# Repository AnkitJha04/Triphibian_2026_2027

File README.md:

# BE Capstone Project

## Project Title

RiftWalker: The Triphibious Bot

---

## Team Details

| Sr. No. | Name of Student | Roll No. | Branch                   | Email ID                      |
|---------|-----------------|----------|--------------------------|-------------------------------|
| 1       | Ankit Jha       | 41       | Automation and Robotics  | 2023.ankitkumar.jha@ves.ac.in |
| 1       | Nidhi Kulkarni  | 15       | Automation and Robotics  | 2023.nidhi.kulkarni@ves.ac.in |
| 1       | Yadnyee Joshi   | 10       | Automation and Robotics  | 2023.yadnyee.joshi@ves.ac.in  |
| 1       | Dnyanam Gala    | 36       | Automation and Robotics  | 2023.dnyanam.gala@ves.ac.in   |

---

## Guide Details

**Project Guide: Mrs. Sangeeta Prasanna Ram**  
**Department:** Automation and Robotics  
**Institute:** VESIT, Mumbai  

---

## Problem Statement

The objective of this project is to create an innovative, small unmanned robotic system that can function in air, land, and water domains through a unified propulsion and control mechanism and thus eliminates the requirement of using different systems such as UAV, UGV, and surface water vehicles in multi-environment missions.

Traditional unmanned systems are usually designed to work in one environment only. While the UAV offers high-speed flying abilities, it lacks endurance; the land robot offers efficiency but is limited by terrain; and the surface vehicle is incapable of crossing land barriers.

Recent studies have shown that integration of these two technologies is possible; however, triphibious robots are far fewer in number compared to dual-environment robots since integration leads to more weight and complexity in design and control, in addition to increased energy consumption.

---

## Abstract

Unmanned robotic systems are being increasingly employed for surveillance purposes, inspection tasks, emergency rescue operations and monitoring of the environment. But since most of these platforms are designed for one environment only, which could be air, land or water, missions in complex environments would either necessitate the use of multiple vehicles or halt the mission as the platform encounters the environment it cannot negotiate. It has been shown through studies on multimodal robots that multimodality is useful in increasing accessibility but it brings with it some difficulties in terms of weight, efficiency, mechanics and control.

The Riftwalker is a prototype of a triphibious robotic platform that aims to study movement in air, land and surface water using the same vehicle architecture. The platform uses four brushless motors as the source of propulsion in aerial environment while servo motors are used to orient the motors for different modes of operation. Passive wheels help the robot move on the ground while elements providing buoyancy help the robot operate in surface water environment.

The current design target has an approximately 2.2 kg maximum take-off mass, with calculated/design-stage performance targets of approximately 58 km/h aerial speed, 78 km/h peak ground speed and 10 km/h surface-water speed. These values will be treated as design targets until experimentally validated.

The expected outcome is a functional prototype demonstrating controlled movement and transition between three operating domains for applications including search and rescue, environmental surveying, inspection and remote reconnaissance.

Youtube video link :- https://youtu.be/WmMp18_r6lU

---

## Objectives

1. To study existing **multimodal and triphibious robotic platforms** and identify the challenges associated with integrating aerial, terrestrial and surface-water mobility into a single robotic system.

2. To develop a **3D CAD model** of the RiftWalker incorporating the structural frame, BLDC motor assemblies, servo-based tilting mechanism, wheels, buoyancy elements and electronics enclosure.

3. To design a **servo-based thrust vectoring mechanism** that changes the orientation of the BLDC propulsion units to enable different modes of locomotion using a unified propulsion system.

4. To perform **engineering calculations and feasibility analysis** including component-wise weight estimation, thrust-to-weight ratio, servo torque, battery and power requirements, land mobility, and water buoyancy.

5. To develop a custom **ESP32-S3 based flight controller PCB** integrating power management, motor and servo interfaces, USB-C programming, battery voltage monitoring and required sensor interfaces.

6. To integrate onboard sensors including the **MPU6050 IMU, magnetometer, barometer, ultrasonic sensor and water sensor** for orientation, altitude, obstacle and environmental-state monitoring.

7. To validate the proposed mechanical and electronic design through **simulation, PCB ERC/DRC verification and prototype testing**, ensuring that the system meets the defined design requirements.

8. To fabricate and integrate the mechanical, electronic and control subsystems and evaluate the **air, land and surface-water operating modes** of the RiftWalker prototype.

9. To document the complete design process, calculations, implementation, testing and results, and identify **future improvements and applications** of the proposed multi-terrain robotic platform.

---

## Scope of the Project

This project will cover the following key areas:

1) **3D mechanical design** and development of the servo-based thrust vectoring mechanism.
2) Selection and integration of **BLDC motors, ESCs, servos, wheels and buoyancy elements**.
3) Design of a custom **ESP32-S3 based flight controller PCB** with sensor, motor and servo interfaces.
4) Integration of sensors including **MPU6050, magnetometer, barometer, ultrasonic and water sensors**.
5) **Engineering calculations and simulation** for weight, thrust, torque, power and buoyancy.
6) Prototype fabrication, hardware integration and **testing of air, land and water operation**.
7) Performance evaluation and documentation of the developed system.

---

## Existing System

Existing unmanned robotic systems are generally designed for operation in a specific environment. They can broadly be classified as follows:

| Platform          | Strength                                               | Main Limitation                                             |
|------------------ |------------------------------------------------------- |------------------------------------------------------------ |
| UAV               | Fast aerial movement and access to difficult locations | High energy consumption and limited endurance               |
| UGV               | Efficient and stable terrestrial operation             | Restricted by water, steep terrain and other obstacles      |
| USV               | Efficient operation on surface water                   | Limited terrestrial mobility                                |
| Dual-Mode Robot   | Capable of operating in two environments               | Cannot independently access the third environment           |
| Triphibious Robot | Potential to operate in air, land and water            | Higher mass, mechanical complexity and control requirements |

Research has demonstrated the feasibility of combining multiple modes of locomotion within a single robotic platform. Existing triphibious and multimodal systems have explored approaches such as shared propulsion systems, tilting or morphing mechanisms and integrated mobility structures.

However, combining three different modes of locomotion introduces several engineering challenges, particularly in terms of **weight, energy efficiency, mechanical complexity, controllability and endurance**.

# Limitations of Existing Systems

1. **Multiple System Requirement:** Using separate UAV, UGV and waterborne platforms increases equipment, transportation and operational complexity.

2. **Limited Endurance:** Aerial systems require continuous thrust to remain airborne, resulting in significant power consumption.

3. **Terrain Limitations:** Ground robots may be restricted by water or difficult terrain, while waterborne platforms cannot easily overcome land-based obstacles.

4. **Increased Mechanical Complexity:** Combining separate propulsion and mobility mechanisms for different environments can increase the overall weight, power requirements and mechanical complexity of the system.

These limitations motivate the development of **RiftWalker**, which investigates the feasibility of combining aerial, terrestrial and surface-water mobility within a single robotic platform while sharing major propulsion, power and control components.

---

## Proposed System

RiftWalker proposes one reconfigurable vehicle rather than three independent vehicles.

Main Idea
The same central platform carries the battery, controller, communication system, sensors and propulsion hardware through all operating modes. Components are reused wherever practical rather than adding an independent propulsion system for every environment.

Operating Principle :
Air Mode
Four A2212-class 1400 KV BLDC motors with 9050 propellers operate in a multicopter configuration. The present design calculations indicate approximately 4.72 kg combined maximum static thrust against a 2.20 kg MTOW, corresponding to a calculated thrust-to-weight ratio of approximately 2.15:1.

Land Mode
The vehicle lands onto its wheel system. Servo-controlled propulsion orientation redirects available thrust to generate terrestrial motion rather than requiring a completely separate high-power traction architecture.

Water Mode
Buoyant wheel/body elements keep the electronics and major structure above the waterline while redirected propulsion produces forward motion across the water surface.

Control System : 
An ESP32-S3-class controller is currently proposed for prototype-level control, handling functions such as:
1) Stabilization/PID control,
2) IMU and navigation sensor processing,
3) Propulsion commands,
4) Servo actuation,
5) Mode management,
6) Telemetry,
7) Waypoint navigation.

Expected Benefits :

The expected benefit is mobility flexibility rather than superior performance in every individual domain.

A purpose-built UAV will likely fly more efficiently, a dedicated UGV can achieve better terrestrial endurance, and a purpose-built USV will generally perform better on water. RiftWalker instead investigates whether somewhat reduced domain-specific efficiency can be accepted in exchange for one platform being able to continue a mission when the terrain changes.
That is a much stronger and more realistic technical proposition.

---

## System Architecture

                    ┌─────────────────────┐
                    │   HUMAN OPERATOR    │
                    │ Ground Control / UI │
                    └──────────┬──────────┘
                               │
                     Telemetry / Commands
                               │
                               ▼
                  ┌────────────────────────┐
                  │ ONBOARD CONTROL SYSTEM │
                  │      ESP32-S3          │
                  │                        │
                  │ • Mission Logic        │
                  │ • PID / Stabilization  │
                  │ • Sensor Fusion        │
                  │ • Mode Management      │
                  │ • Navigation           │
                  └───────┬────────┬───────┘
                          │        │
                 ┌────────┘        └───────────┐
                 ▼                             ▼
        ┌─────────────────┐          ┌─────────────────┐
        │ SENSOR SYSTEM   │          │ ACTUATION       │
        │                 │          │ SYSTEM          │
        │ IMU             │          │                 │
        │ GNSS / NavIC    │          │ 4 × ESC         │
        │ Altitude        │          │ 4 × BLDC        │
        │ Camera*         │          │ Vector Servos   │
        └─────────────────┘          └────────┬────────┘
                                             │
                         ┌───────────────────┼──────────────────┐
                         ▼                   ▼                  ▼
                    AIR MODE            LAND MODE          WATER MODE
                    Multirotor          Wheels +           Buoyancy +
                    Flight              Vector Thrust      Vector Thrust
                         │                   │                  │
                         └───────────────────┼──────────────────┘
                                             ▼
                                  MULTI-DOMAIN MOBILITY

                     ┌─────────────────────────────┐
                     │       POWER SYSTEM          │
                     │  4S 6200 mAh LiPo Battery   │
                     │  Power Distribution / BEC   │
                     └─────────────────────────────┘

## System Architecture

The RiftWalker system architecture is divided into four main sections:

Control System: The onboard controller acts as the brain of the robot. It processes sensor data, manages stabilization and navigation, controls propulsion, and switches between air, land, and water modes.
Sensor & Navigation System: Sensors such as the IMU and GNSS/NavIC provide information about orientation, position, motion, and vehicle state. Additional cameras or perception sensors can be integrated for autonomous navigation.
Propulsion & Actuation System: Four BLDC motors with ESCs generate thrust. Servo mechanisms change the direction of the propulsion system depending on the operating mode—vertical thrust for flight and redirected thrust for movement on land or water.
Power & Communication System: A 4S 6200 mAh LiPo battery supplies the motors, servos, controller, and sensors. A wireless telemetry link allows the ground operator to send commands and receive vehicle data.

Overall, the architecture is designed around sharing the same propulsion, power, sensing, and control hardware across all three environments, reducing the need for separate systems for each mode.

---

## Hardware Requirements

| Sr. No. | Component               | Specification                      | Quantity | Purpose                                           |
| ------- | ----------------------- | ---------------------------------- | -------- | ------------------------------------------------- |
| 1       | BLDC Motor              | A2212, 1400 KV                     |        4 | Common propulsion for air, land and water         |
| 2       | Propeller               | 9050, matched to motor             |        4 | Generates aerodynamic thrust                      |
| 3       | ESC                     | 4S-compatible, appropriately rated |        4 | Controls BLDC motor speed                         |
| 4       | LiPo Battery            | 4S, 6200 mAh                       |        1 | Main onboard power source                         |
| 5       | Microcontroller         | ESP32-S3                           |        1 | Main control, sensor processing and telemetry     |
| 6       | IMU                     | 6/9-axis accelerometer + gyroscope |        1 | Orientation, motion and stabilization             |
| 7       | Sensor (Water/Distance) | Relevent to the use case           |        1 | Outdoor positioning and navigation                |
| 8       | Servo Motors            | High-torque, metal-gear            |        4 | Changes propulsion orientation between modes      |
| 9       | Wheels                  | Lightweight passive/free-rolling   |        4 | Supports terrestrial locomotion                   |
| 10      | Buoyancy System         | Lightweight waterproof floats/body |    1 set | Provides stability and flotation on water         |
| 11      | Power Distribution/BEC  | 4S compatible                      |        1 | Distributes and regulates electrical power        |
| 12      | Telemetry System        | Wireless bidirectional link        |        1 | Operator commands and vehicle telemetry           |
| 13      | Camera                  | Lightweight onboard camera         |        1 | Visual feedback/perception                        |
| 14      | Frame & Mounting System | Lightweight rigid structure        |        1 | Supports all mechanical and electronic components |
| 15      | Flight Controller       | Custom                             |        1 | For functioning of everything perfectly           |
---

## Software Requirements

| Sr. No. | Software / Tool          | Version           | Purpose                                          |
| ------- | ------------------------ | ----------------- | ------------------------------------------------ |
| 1       | Arduino IDE / PlatformIO | Current stable    | ESP32-S3 firmware development                    |
| 2       | Embedded C/C++           | Current toolchain | Low-level control and sensor interfacing         |
| 3       | Python                   | 3.x               | Data analysis, testing and algorithm prototyping |
| 4       | MATLAB / Simulink        | Available release | Modelling, PID tuning and system analysis        |
| 5       | Inventor                 | Available release | Mechanical CAD and assembly design               |
| 6       | KiCad                    | Current stable    | PCB and electronic system design                 |
| 7       | Git / GitHub             | Current stable    | Version control and project documentation        |
| 8       | SimScale / OpenFOAM      | Current stable    | Computational Fluid Dynamics (CFD) simulation    |
| 9       | Wokwi                    | Current stable    | Headless hardware testing prior to flashing.     |

---

## Technologies Used

1. **Embedded Systems:** ESP32-S3 and Embedded C/C++ for vehicle control and sensor interfacing.
2. **Sensor Integration & Control:** Integration of IMU, magnetometer, barometer, ultrasonic and water sensors for vehicle-state monitoring and control.
3. **PID Control:** PID-based stabilization and control of the propulsion system and vehicle motion.
4. **PCB Design (EDA):** KiCad for schematic design, component selection, PCB layout, routing and ERC/DRC verification.
5. **CAD & Mechanical Design:** Autodesk Inventor for 3D modelling, assembly design and development of the mechanical structure.
6. **Thrust Vectoring:** Servo-controlled motor orientation for redirecting propulsion across different operating modes.
7. **Multirotor Propulsion:** BLDC motors, ESCs and propellers for aerial propulsion.
8. **Power Management:** Separate logic and servo power domains with battery voltage monitoring and regulated power supplies.
9. **Wireless Communication:** Wireless communication for vehicle control and telemetry.
10. **Simulation & Engineering Analysis:** Mechanical and system-level analysis along with calculations for weight, thrust-to-weight ratio, servo torque, power requirements and buoyancy.

---

## Methodology

1. **Literature Survey:** Study existing multimodal and triphibious robotic platforms to understand their propulsion mechanisms, mobility approaches, control strategies and limitations.
2. **Problem Identification and Requirement Analysis:** Identify the major challenges involved in combining air, land and water mobility and establish the mechanical, electrical and performance requirements of RiftWalker.
3. **Concept Development:** Evaluate different multi-terrain mechanisms and finalize the use of a unified BLDC propulsion system with a **servo-based thrust vectoring mechanism**.
4. **Mechanical Design:** Develop the **3D CAD model in Fusion 360**, including the structural frame, motor mounts, servo tilting mechanism, wheels, buoyancy elements and electronics enclosure.
5. **Engineering Analysis:** Perform weight estimation, thrust-to-weight ratio, servo torque, battery and power, land mobility and buoyancy calculations to evaluate the feasibility of the proposed design.
6. **Simulation and Design Validation:** Validate the proposed mechanical concept and operating principle through simulation and analysis, and modify the design based on the obtained results.
7. **Electronic System Development:** Design the custom **ESP32-S3 based flight controller PCB** in KiCad, including power management, motor and servo interfaces, sensor interfaces, USB-C programming and battery monitoring.
8. **PCB Verification and Hardware Integration:** Perform schematic checks, ERC/DRC verification and PCB routing, followed by fabrication and integration of the controller with the motors, servos, sensors and power system.
9. **Firmware and Control Development:** Develop the ESP32-S3 firmware for sensor processing, stabilization, motor and servo control, communication and operating-mode management.
10. **Testing and Validation:** Test the integrated prototype in air, land and surface-water modes and evaluate parameters such as stability, mobility, thrust-vectoring response, power consumption and transition behaviour.
11. **Performance Analysis and Documentation:** Compare experimental results with calculated design values, identify limitations and improvements, and document the complete design, implementation and testing process.

---

## Project Timeline

| Week / Month |                      Task Planned                                  | Status      |
|--------------|--------------------------------------------------------------------|-------------|
| **Week 1**   | Problem Finalization & Project Planning                            | Completed   |
| **Week 2**   | Literature Survey & Research Paper Review                          | Completed   |
| **Week 3**   | Requirement Analysis & Component Selection                         | Completed   |
| **Week 4**   | Engineering Calculations                                           | Completed   |
| **Week 5**   | Mechanical Design & 3D CAD Modelling                               | Completed   |
| **Week 6**   | Simulation & Design Validation                                     | Completed   |
| **Week 7**   | Flight Controller PCB Design & Schematic Development               | Completed   |
| **Week 8**   | PCB Routing, ERC/DRC Verification & Hardware Procurement           | Completed   |
| **Week 9**   | PCB ic finalization & Component Weight testing                     | Completed   |
| **Week 10**  | PCB Fabrication & Assembly                                         | In Progress |
| **Week 11**  | Hardware Integration & Sensor Interfacing                          | In Progress |
| **Week 12**  | Firmware Development & System Testing                              | In Progress |
| **Week 13**  | Final Testing, Documentation & Project Demonstration               | Pending     |
| **Week 14**  | Research Paper Writing & Project Documentation                     | Pending     |
| **Week 15**  | Final Presentation & Project Demonstration                         | Pending     |

---

## Weekly Progress Updates

Students must update this section every week.
| Week  | Date        |                  Work Completed                |             Next Week         |         Issues / Challenges       | GitHub Commit |
|------ |------------ |----------------------------------------------- |------------------------------ |---------------------------------- |-------------- |
| **1** | 22/06–28/06 | Problem finalization & planning                | Literature survey             | Concept feasibility               | —             |
| **2** | 29/06–05/07 | Literature survey & paper review               | Requirement analysis          | Mobility vs. weight               | —             |
| **3** | 06/07–12/07 | Requirements & components finalized            | Engineering calculations      | Weight, thrust & cost             | —             |
| **4** | 13/07–19/07 | Weight, thrust, torque & buoyancy calculations | Mechanical design             | Maintaining low weight            | —             |
| **5** | 20/07–26/07 | 3D CAD model & mechanical design               | Design validation & PCB       | Mechanism integration             | —             |
| **6** | 27/07–02/08 | Design validation & simulation                 | PCB schematic                 | Mechanical-electronic integration | —             |
| **7** | 03/08–09/08 | ESP32-S3 schematic & component selection       | PCB routing & verification    | GPIO & power management           | —             |
| **8** | 10/08–16/08 | PCB routing, ERC/DRC & documentation           | PCB fabrication & procurement | Routing & component placement     | —             |
| **9** | 17/08–23/08 | Finalized and Completed PCB design verification| Working on software           | Component availability            | —             |
| **10**| 24/08–30/08 | Made control center to control/code the drone  | PCB fabrication & procurement | Software needs and api development| —             |

---

## Design Files

| File Type             | File Name / Link                                 | Description                                          |
|--                     |---                                               |---                                                   |
| **CAD Model**         | [Autodesk Inventor CAD Files](hardware/CAD/)     | 3D mechanical model and assembly of RiftWalker       |
| **Circuit Diagram**   | [Circuit Diagram ](images/circuit_diagram-2.jpg) | Custom ESP32-S3 flight-controller schematic          |
| **PCB Design**        | [KiCad PCB Files](hardware/PCB/)                 | Custom flight-controller PCB design and routing      |
| **ERC / DRC Reports** | [PCB Verification Files](hardware/PCB/)          | Electrical and design rule verification reports      |
| **Flowchart**         | [System Flowchart](images/flowchart.jpeg)        | Proposed operating sequence and control flow         |
| **Simulation File**   | [Wokwi Simulation Files](software/simulation/)   | ESP32-based simulation files for preliminary testing |        

---

## Circuit Diagram

---

## Flowchart / Algorithm

### Algorithm

1. System Initialization – Power up the ESP32-S3 and initialize the IMU, GNSS/NavIC, altitude sensor, ESCs, servos and communication modules.
2. Self-Test & Health Check – Verify sensor communication, battery voltage, telemetry link and actuator status. Prevent arming if a critical fault is detected.
3. Standby / Arm – Keep propulsion disabled until a valid arm command and mission/operator command are received.
4. Sensor Acquisition – Continuously collect orientation, acceleration, altitude, position and other available sensor measurements.
5. Sensor Fusion & State Estimation – Combine measurements to estimate the robot's attitude, position, velocity and motion state.
6. Control Loop – Run the feedback controllers at high frequency to calculate the required thrust, attitude and motion corrections.
7. Mode Decision – Determine whether Air, Land or Water mode is requested/appropriate. For the prototype, operator-confirmed switching is safer than claiming fully autonomous terrain classification.
8. Execute Selected Mode – In Air Mode, operate as a multirotor; in Land Mode, redirect thrust and use the wheels; in Water Mode, maintain flotation and use vectored thrust for surface movement.
9. Navigation – Follow manual commands or mission waypoints while continuously updating the required heading, speed and position.
10. Safety Monitoring – Continuously check battery level, communication link, attitude, actuator/current limits and other available health information.
11. Failsafe Handling – If a critical fault occurs, execute the safest response available for the current mode, such as controlled landing, stopping propulsion, remaining afloat, or returning to a safe location where technically feasible.
12. Telemetry & Logging – Transmit vehicle status to the ground station and record important sensor, control and fault information.
13. Mission Check – If the mission is incomplete, return to the sensing/control loop. If complete, move to shutdown.
14. Safe Shutdown – Stop the mission, disarm propulsion and place actuators in their safe state.

---

## Implementation Details

The implementation of the RiftWalker project is divided into tightly integrated hardware and software phases, completely bypassing off-the-shelf drone kits in favor of a custom-engineered multi-domain architecture.

Hardware Implementation
Mechanical Frame & Buoyancy: The chassis utilizes custom Z-shaped carbon-fiber arms to elevate the propeller arcs, preventing aerodynamic thrust-blockage. Closed-cell XPS foam wheels are underslung on the chassis, providing mechanical ground clearance for land operations and acting as highly buoyant pontoons to keep the waterline below the main electronics bay during marine operations.

Actuation & Propulsion: The drive system relies on four BLDC motors mounted on rotating vectoring hubs. These hubs are actuated by high-torque DS3218 digital servos capable of sweeping the entire propulsion system 90 degrees forward for surface travel.

Custom Electronics (PCB): A custom-designed ESP32-S3 flight controller serves as the system's brain.

Power Distribution: The board features an isolated dual-power architecture. A high-current 5V rail (with a large bulk capacitor) drives the vectoring servos, while a dedicated AP2112K LDO regulator provides clean 3.3V power to the logic circuits, preventing brownouts.

Sensors: An MPU-6050 IMU and MS5607 barometer are mounted on the bottom layer of the PCB to shield them from thermal output and RF noise. An HC-SR04 ultrasonic sensor is integrated using a hardware voltage divider to safely step down the 5V echo pulse to the 3.3V logic level.

Software Implementation
Firmware Architecture: To handle the shape-shifting mechanics, the firmware was written entirely from scratch using C++ and FreeRTOS, bypassing the limitations of standard multirotor software.

Dual-Core Processing: The ESP32-S3’s dual-core capabilities are fully leveraged to ensure real-time stability:

Core 0 (Sensor Fusion): Dedicated exclusively to polling the IMU, barometer, and ultrasonic sensors. It calculates altitude and pressure to autonomously detect the operating domain (Air, Land, or Water).

Core 1 (Motor & PID Control): Strictly isolated to handle the high-speed PID stabilization loops and PWM timing for the ESCs and servos.

Concurrency & Safety: Hardware mutex locks are implemented to allow the two cores to share telemetry data safely. This guarantees that environmental sensor reads never delay the critical motor control loops, enabling instantaneous thrust-vectoring when transitioning between terrains.

## Code Structure

```text
BE-Capstone-Project/
│
├── README.md
│
├── docs/
│   └──  literature_survey.md
│
├── hardware/
│   ├── hardware.md
│   ├── pcb_design/
|       ├── DRC.rpt
|       ├── ERC.rpt
|       ├── Flight Controller.kicad_pcb
|       ├── Flight Controller.kicad_prl
|       ├── Flight Controller.kicad_pro
|       ├── Flight Controller.kicad_sch
|       ├── PCB Dimensions.png
|       ├── IC bom.xlsx
|       ├── README.md
|       └── fp-info-cache
│   ├── Actual_Fly_Control
|       ├── Actual_Fly_Control.ino
|       ├── RiftwalkerConfig.h
|       └── RiftwalkerProtocol.h
│   ├── Callibration_Code
|       └── Callibration_Code.ino
│   ├── ESP_NOW_Ground_Transmitter
|       ├── ESP_NOW_Ground_Transmitter.ino
|       └── RiftwalkerProtocol.h
│   ├── I2C_Scanner
|       └── I2C_Scanner.ino
│   └── cad_model
|       ├── BLDC Holder.ipt
|       ├── BLDC Holder.stl
|       ├── Bearing.ipt
|       ├── Bearing.stl
|       ├── Body.ipt
|       ├── Body.stl
|       ├── Connecting Rod.ipt
|       ├── Connecting Rod.stl
|       ├── Final Body.iam
|       ├── Holder Cover.ipt
|       ├── Holder Cover.stl
|       ├── Motor.ipt
|       ├── Propeller.ipt
|       ├── README.md
|       ├── Servo.ipt
|       ├── Pcb Spacer.stl
|       ├── TEST ASSEMBLY 1.stl
|       ├── Top Cover.ipt
|       ├── Top Cover.stl
|       ├── Tyres.stl
|       └── Tyres.ipt
│
├── software/
│   ├── software.md
│   └── simulation/
|       ├── README.md
|       ├── diagram.json
|       ├── libraries.txt
|       ├── sketch.ino
|       └── wokwi-project.txt
|   └── Command and Control Center/
|       ├── README.md
|       ├── app.py
|       ├── bridge.py
|       ├── requirements.txt
|       ├── requirements-web.txt
|       ├── run_desktop.bat
|       ├── run_web.bat
|       ├── VERSION.txt
|       ├── FIRMWARE_BUILD.md
|       ├── GROUND_BRIDGE_SETUP.md
|       ├── HARDWARE_PINOUT.md
|       ├── SERIAL_PROTOCOL.md
|       ├── TUNING_GUIDE.md
|       ├── VALIDATION_CHECKLIST.md
|       ├── RELEASE_MANIFEST.txt
|       ├── RELEASE_NOTES_HARDWARE_V1.md
|       ├── Web/
|           └── index.html
|       └── tests/
|           ├── test_bridge.py
|           └── test_ms5607_compensation.py
│
├── images/
|   ├── circuit_diagram-2.jpg
|   ├── circuit_diagram.jpeg
|   ├── flowchart.jpeg
|   ├── images.md
|   └── system_architecture.jpeg
│
└── references/
    └── paper.md
```

---

## How to Run the Project

### Step 1: Clone the Repository

```bash
git clone https://github.com/username/project-name.git
```

### Step 2: Install Dependencies

```bash
pip install -r requirements.txt
```

or mention specific software/library installation steps.

### Step 3: Upload / Run the Code

```bash
python main.py
```

or

```bash
arduino-cli upload -p COMx --fqbn board_name
```

### Step 4: Observe the Output

When powered, the RiftWalker initializes its IMU and establishes a secure ESP-NOW link with the ground station, displaying battery voltage and current vector angles. Upon command, the craft can spool its motors to take off vertically like a standard drone, demonstrating stable hover capabilities. When the operator engages "Surface Mode," the servos smoothly rotate the motor arms $90^\circ$ forward while adjusting thrust to prevent altitude loss. On the ground or water, the vehicle utilizes differential aero-thrust to steer and propel itself forward at high speeds, gliding on its XPS wheels with a drastically reduced current draw compared to hovering.

---

## Testing and Results

| Test No. | Test Description | Expected Result | Actual Result | Status      |
| -------- | ---------------- | --------------- | ------------- | ----------- |
| 1        |                  |                 |               | Pass / Fail |
| 2        |                  |                 |               | Pass / Fail |
| 3        |                  |                 |               | Pass / Fail |

---

## Result Images / Videos

Add images or videos of the working prototype.

```markdown

```

Video Link:

```markdown
[Project Demo Video](https://drive.google.com/your-video-link)
```

---

## Applications

1. Post-Disaster Search & Rescue (SAR): Navigating through flooded urban environments, blocked roads, and debris dams where neither standard boats nor ground rovers can pass.
2. Hazardous Environmental Monitoring: Surveying toxic lakes, unstable wetlands, or swamp ecosystems without the risk of underwater propellers getting tangled in aquatic vegetation.
3. Tactical Reconnaissance & Border Patrol: Serving as a covert, multi-terrain sentinel capable of flying to a location rapidly and transitioning to a low-power, silent ground/water crawl for long-term observation.
4. Amphibious Ship-to-Shore Scouting: Launching from a naval vessel, flying to the coastline, and seamlessly driving onto the beach to conduct physical surveys.
ETC.

---

## Advantages

1. Elimination of Drivetrain Bloat: Achieves an exceptional 2.15:1 thrust-to-weight ratio by using a single set of aero-propellers for all terrains, eliminating the dead-weight of separate wheel motors and heavy gearboxes.
2. Exponential Endurance Gains: By dropping to the ground or water and operating as an aero-propelled rover, mission endurance is extended from a maximum of ~9.5 minutes in the air up to ~54.5 minutes on the surface.
3. Passive Buoyancy & Suspension: The lightweight XPS foam wheels serve a dual purpose, acting as excellent shock absorbers for rough terrain and fail-safe, unsinkable flotation hulls for water traversal.
4. Cost-Effective & Scalable: By eliminating redundant drive hardware and integrating a custom ESP32-based flight controller, the unit cost is drastically reduced compared to commercial military-grade amphibious systems.

---

## Limitations

1. Transition Vulnerability: The physical transition phase takes  seconds, during which the craft is highly susceptible to sudden crosswinds or aerodynamic stalling if not perfectly timed.
2. Ground Clearance Ceilings: Terrestrial obstacle clearance is strictly limited by the radius of the XPS wheels; the vehicle cannot drive over boulders or deep trenches without reverting to flight mode.
3. Acoustic Signature: Using aero-propulsion to drive on land generates significantly more noise (propeller wash) than a traditional electric wheeled rover, reducing its stealth capabilities in close-proximity scenarios.
4. Thermal Constraints: When planing on water at high throttle for extended periods, the enclosed central electronics box lacks active airflow cooling, potentially leading to thermal throttling of the ESCs.
   
---

## Future Scope

1. Autonomous AI Integration: Upgrading the processing core to incorporate a lightweight AI vision module (e.g., using the ESP32-S3's vector instructions or an external neural accelerator) for autonomous optical obstacle avoidance.
2. Triple-Redundant Aerospace Sensing: Developing a "V2" PCB that utilizes triple-redundant IMUs and Barometers connected via an SPI bus to create a fault-tolerant voting architecture for military-grade reliability.
3. BVLOS Telemetry Upgrade: Replacing the 2.4GHz ESP-NOW link with a secure, AES-encrypted Long Range (LoRa) 915MHz telemetry module for Beyond Visual Line of Sight (BVLOS) operations.
4. Aquatic Self-Righting Mechanism: Engineering an automated algorithmic response or physical mass-shifting mechanism to ensure the craft can self-right and recover if flipped upside down by heavy waves in water mode.
   
---

## Research Paper / Publication

| Item                      | Details                                                   |
| ------------------------- | --------------------------------------------------------- |
| Paper Title               |                                                           |
| Conference / Journal Name |                                                           |
| Paper Status              | Not Started / Drafting / Submitted / Accepted / Published |
| Submission Date           |                                                           |
| Paper Link                |                                                           |

---

## References

[1] G. Zhong, J. Cao, X. Chai, and Y. Bai, "Design and Performance Analysis of a Triphibious Robot with Tilting-Rotor Structure," *IEEE Access*, vol. 9, pp. 10871–10879, 2021, doi: 10.1109/ACCESS.2021.3050182.

[2] X. Li, M. Lai, M. Zhang, J. Lin, T. Lai, J. Zhi, C. Xu, F. Gao, Y. Cao, "TriphiBot: A Triphibious Robot Combining FOC-based Propulsion with Eccentric Design," arXiv preprint arXiv:2602.01385, 2026.

[3] M. Xia, B. Wang, and Z. Luo, "Design and Experiment of a Multimodal Aerial Aquatic Vehicle with Morphing Wing and Tilting Rotors," *Advances in Mechanical Engineering*, vol. 17, 2025, doi: 10.1177/16878132251319142.

[4] S. L. Pradeep Kumar, B. Deeban, D. Santhosh Kumar, and M. Sasi Kumar, "Design and Fabrication of a Multi-Terrain Triphibian Quadcopter for Airborne, Terrestrial, and Aquatic Mobility," *Discover Mechanical Engineering*, vol. 5, art. no. 20, 2026, doi: 10.1007/s44245-025-00167-7.

[5] Z. Zheng, Q. Cai, J. Wang, X. Xu, M. Cao, H. Yu, J. Li, J. Meng, and G. Lu, "CapsuleBot: A Novel Hybrid Aerial-Ground Bi-Copter Robot With Two Actuated-Wheel-Rotors," *IEEE Robotics and Automation Letters*, vol. 10, no. 1, pp. 120–127, 2025, doi: 10.1109/LRA.2024.3504232.

---

## Repository Update Guidelines

Each student team must update the GitHub repository regularly.

Minimum expected updates:

* Update README every week.
* Push code changes regularly.
* Upload circuit diagrams, CAD files, PCB files, reports and presentations.
* Add weekly progress in the progress table.
* Maintain proper folder structure.
* Do not upload unnecessary temporary files.
* Each major update should have a meaningful commit message.

Example commit messages:

```text
Added problem statement and objectives
Updated system architecture diagram
Added sensor interfacing code
Updated weekly progress for Week 3
Added testing results and prototype images
```

---

## Declaration

We declare that this project work is carried out by our team as part of the BE Capstone Project. The work will be regularly updated on GitHub and all references used will be properly cited.

---

## License

This project is for academic use only.

Optional:

```text
MIT License / Creative Commons / Institute Use Only
```

```
```

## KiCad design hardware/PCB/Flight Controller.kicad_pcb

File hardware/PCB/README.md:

# RiftWalker PCB Design

This folder contains the KiCad schematic, PCB layout and verification files for the custom ESP32-S3 flight controller.

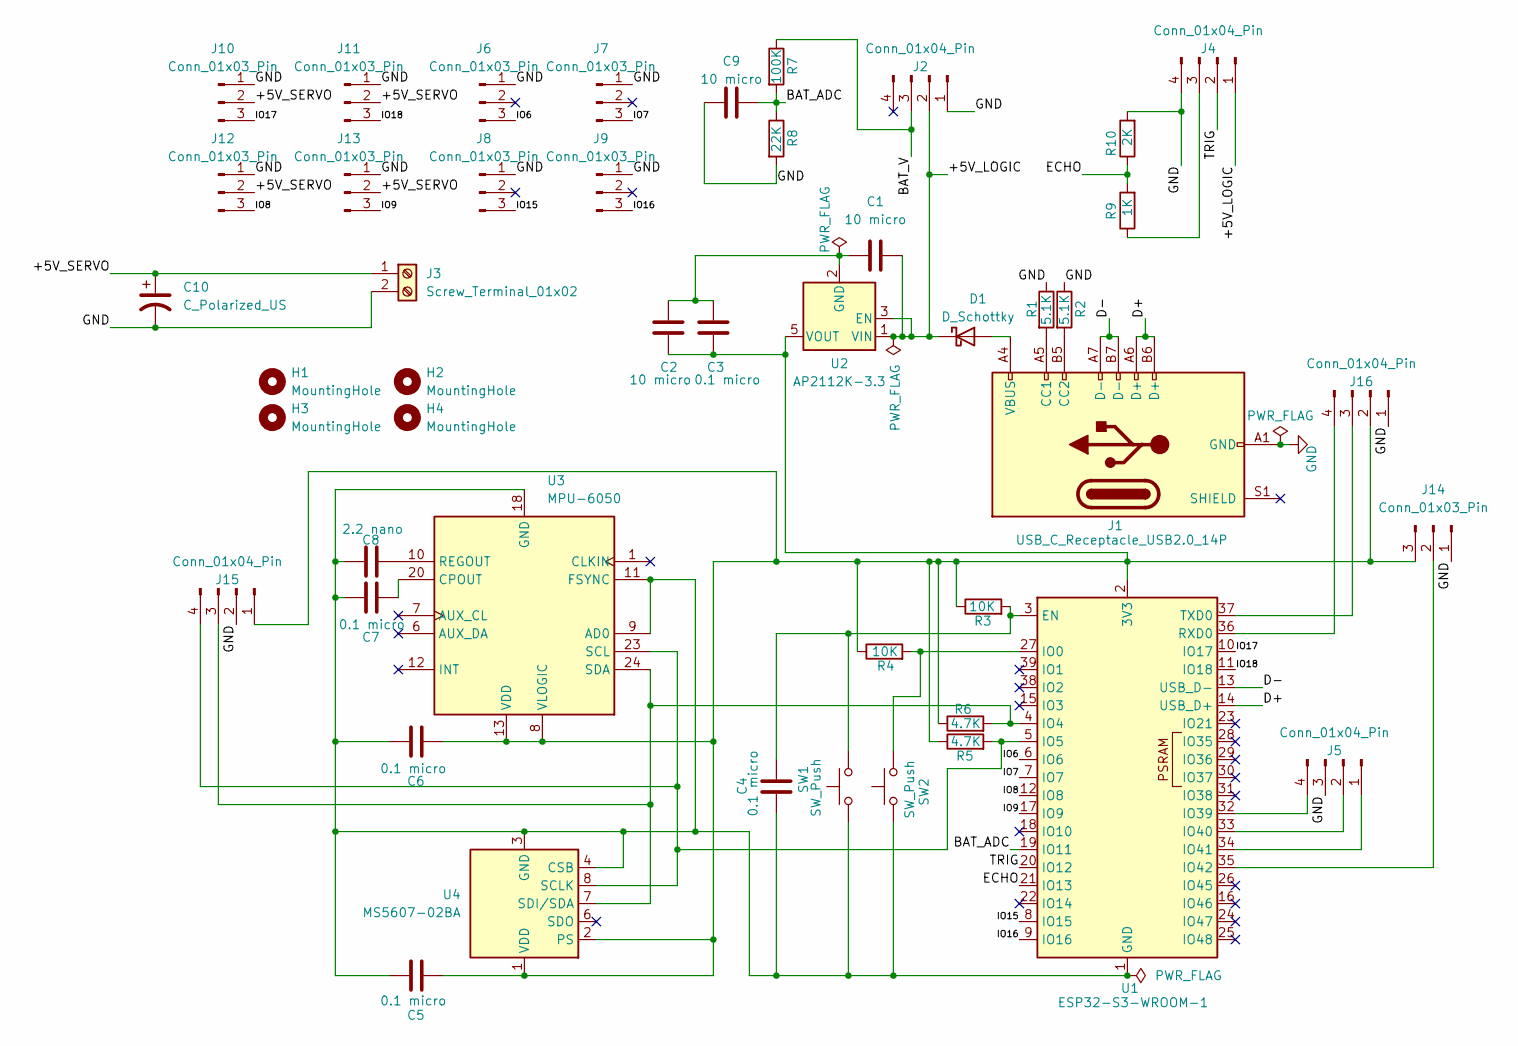
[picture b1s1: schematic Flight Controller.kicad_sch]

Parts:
C1, C2, C9: 10 micro; C_0805_2012Metric
C3, C4, C5, C6, C7: 0.1 micro; C_0805_2012Metric
C8: 2.2 nano; C_0805_2012Metric
C10: C_Polarized_US; CP_Radial_D10.0mm_P5.00mm
D1: D_Schottky; D_SOD-123
H1, H2, H3, H4: MountingHole; MountingHole_3.2mm_M3
J1: USB_C_Receptacle_USB2.0_14P; USB_C_Receptacle_HRO_TYPE-C-31-M-12
J2, J4, J5, J15, J16: Conn_01x04_Pin; JST_XH_B4B-XH-A_1x04_P2.50mm_Vertical
J3: Screw_Terminal_01x02; TerminalBlock_Phoenix_MKDS-1,5-2-5.08_1x02_P5.08mm_Horizont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
J6, J7, J8, J9, J10, J11, J12, J13: Conn_01x03_Pin; PinSocket_1x03_P2.54mm_Vertical
J14: Conn_01x03_Pin; PinHeader_1x03_P2.54mm_Vertical
R1, R2: 5.1K; R_0805_2012Metric
R3, R4: 10K; R_0805_2012Metric
R5, R6: 4.7K; R_0805_2012Metric
R7: 100K; R_0805_2012Metric
R8: 22K; R_0805_2012Metric
R9: 1K; R_0805_2012Metric
R10: 2K; R_0805_2012Metric
SW1, SW2: SW_Push; SW_SPST_B3U-1000P
U1: ESP32-S3-WROOM-1
U2: AP2112K-3.3; SOT-23-5
U3: MPU-6050; QFN-24-1EP_4x4mm_P0.5mm_EP2.15x2.15mm
U4: MS5607-02BA; LGA-8_3x5mm_P1.25mm

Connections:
/+5V_LOGIC: C1.2, D1.1 (K), J2.2, J4.1, U2.1 (VIN), U2.3 (EN)
/+5V_SERVO: C10.1, J3.1, J10.2, J11.2, J12.2, J13.2
/BAT_ADC: C9.2, R7.2, R8.1, U1.19 (IO11)
/BAT_V: J2.3, R7.1
/D+: J1.A6 (D+), J1.B6 (D+), U1.14 (USB_D+)
/D-: J1.A7 (D-), J1.B7 (D-), U1.13 (USB_D-)
/ECHO: R9.2, R10.1, U1.21 (IO13)
/IO6: J6.3, U1.6 (IO6)
/IO7: J7.3, U1.7 (IO7)
/IO8: J12.3, U1.12 (IO8)
/IO9: J13.3, U1.17 (IO9)
/IO15: J8.3, U1.8 (IO15)
/IO16: J9.3, U1.9 (IO16)
/IO17: J10.3, U1.10 (IO17)
/IO18: J11.3, U1.11 (IO18)
/TRIG: J4.2, U1.20 (IO12)
GND: C9.1, C10.2, J1.A1 (GND), J1.A12 (GND), J1.B1 (GND), J1.B12 (GND), J2.1, J3.2, J4.4, J5.3, J6.1, J7.1, J8.1, J9.1, J10.1, J11.1, J12.1, J13.1, J14.1, J15.2, J16.1, R1.1, R2.1, R8.2, R10.2
unnamed: D1.2 (A), J1.A4 (VBUS), J1.A9 (VBUS), J1.B4 (VBUS), J1.B9 (VBUS)
unnamed: J1.A5 (CC1), R1.2
unnamed: J1.B5 (CC2), R2.2
unnamed: J4.3, R9.1
unnamed: J5.1, U1.34 (IO41)
unnamed: J5.2, U1.33 (IO40)
unnamed: J5.4, U1.32 (IO39)
unnamed: J14.2, U1.35 (IO42)
unnamed: C2.2, C3.2, C5.2, C6.2, J14.3, J15.1, J16.2, R3.1, R4.1, R5.1, R6.1, U1.2 (3V3), U2.5 (VOUT), U3.8 (VLOGIC), U3.13 (VDD), U4.1 (VDD), U4.2 (PS)
unnamed: J15.3, R6.2, U1.4 (IO4), U3.24 (SDA), U4.7 (SDI/SDA)
unnamed: J15.4, R5.2, U1.5 (IO5), U3.23 (SCL), U4.8 (SCLK)
unnamed: J16.3, U1.37 (TXD0)
unnamed: J16.4, U1.36 (RXD0)
unnamed: C4.1, R3.2, SW1.2, U1.3 (EN)
unnamed: R4.2, SW2.2, U1.27 (IO0)
unnamed: C1.1, C2.1, C3.1, U2.2 (GND)
unnamed: C4.2, C5.1, C6.1, C7.1, C8.1, SW1.1, SW2.1, U1.1 (GND), U1.40 (GND), U1.41 (GND), U3.9 (AD0), U3.11 (FSYNC), U3.18 (GND), U4.3 (GND), U4.4 (CSB), U4.5 (CSB)
unnamed: C7.2, U3.20 (CPOUT)
unnamed: C8.2, U3.10 (REGOUT)

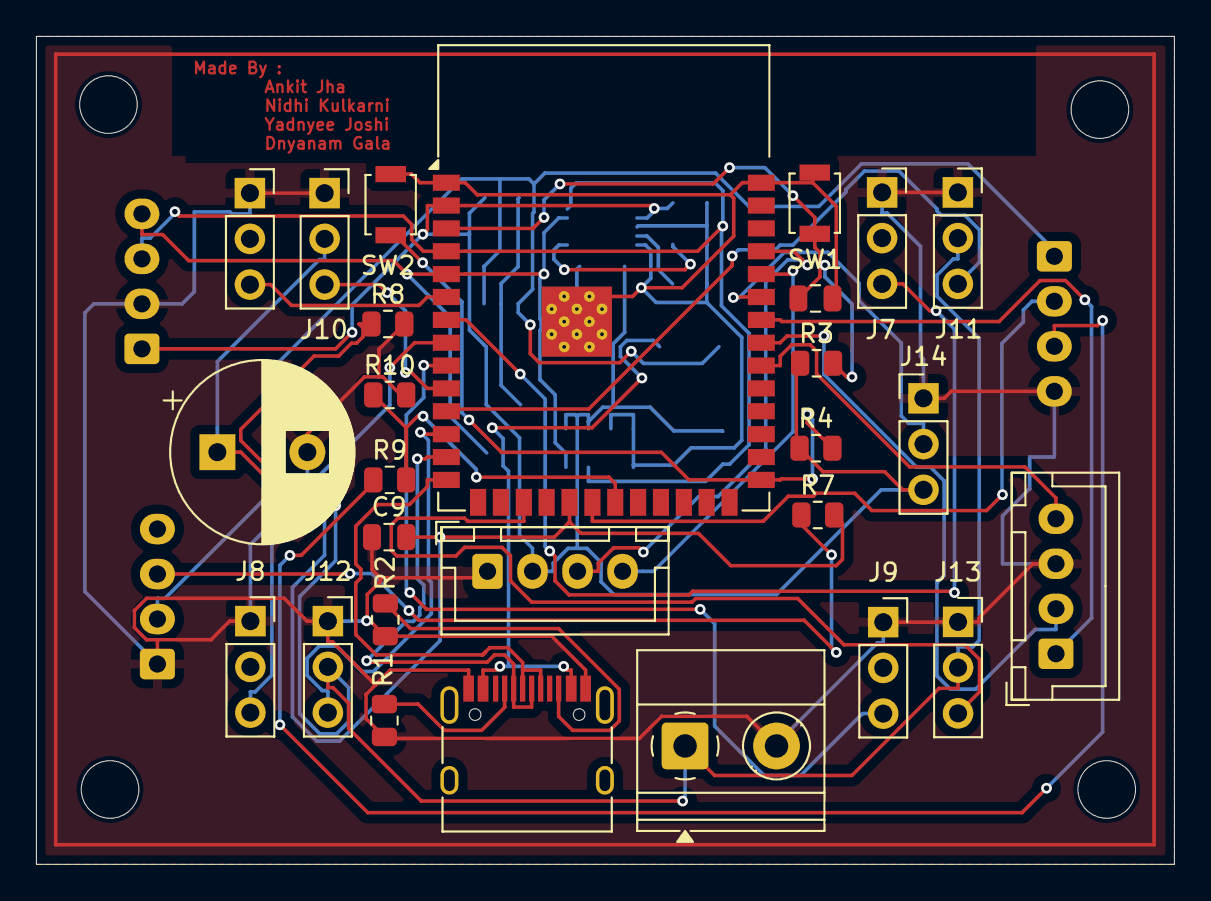
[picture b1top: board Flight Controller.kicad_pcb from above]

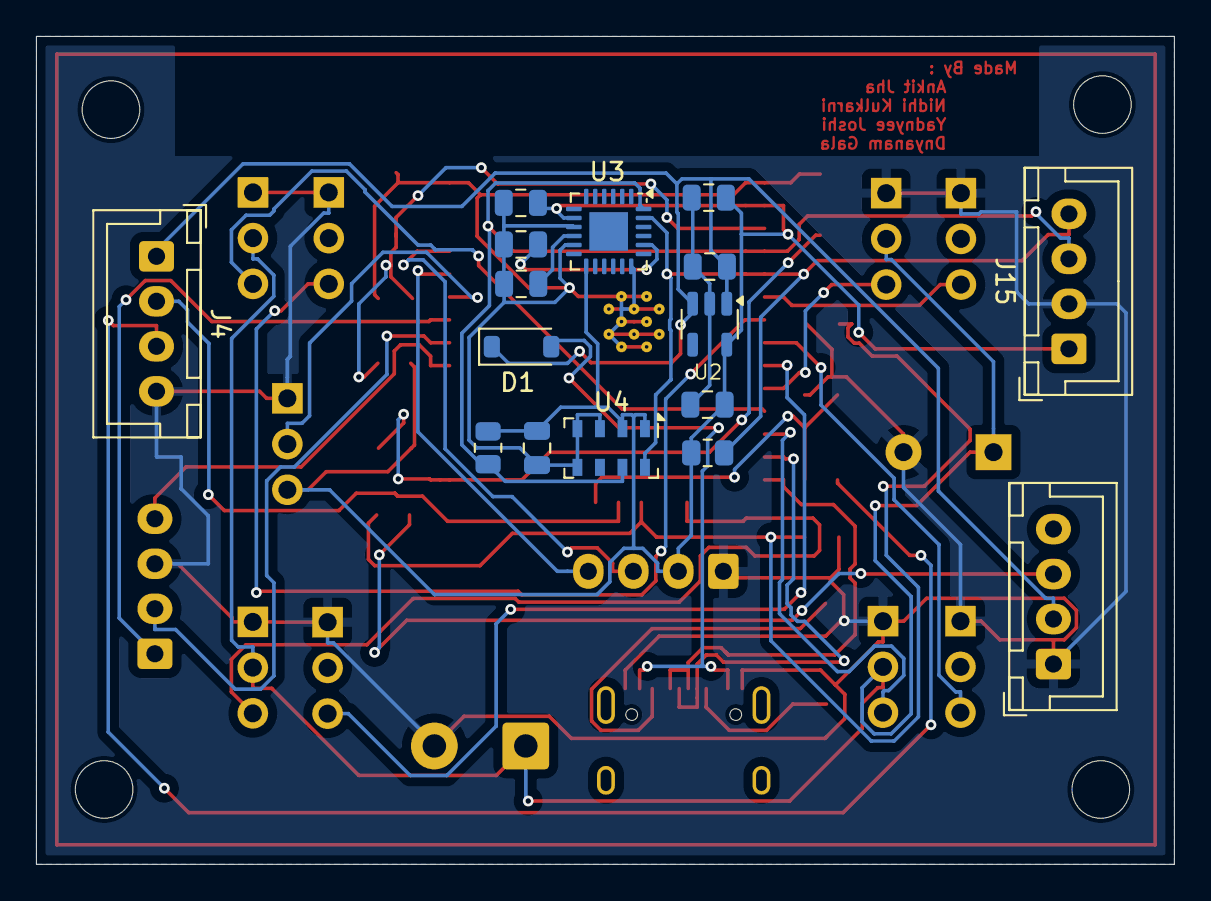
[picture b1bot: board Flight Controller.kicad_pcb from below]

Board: 2 copper layers, 63.2 x 46.0 mm, 47 parts (16 on the bottom side), 36 nets.
